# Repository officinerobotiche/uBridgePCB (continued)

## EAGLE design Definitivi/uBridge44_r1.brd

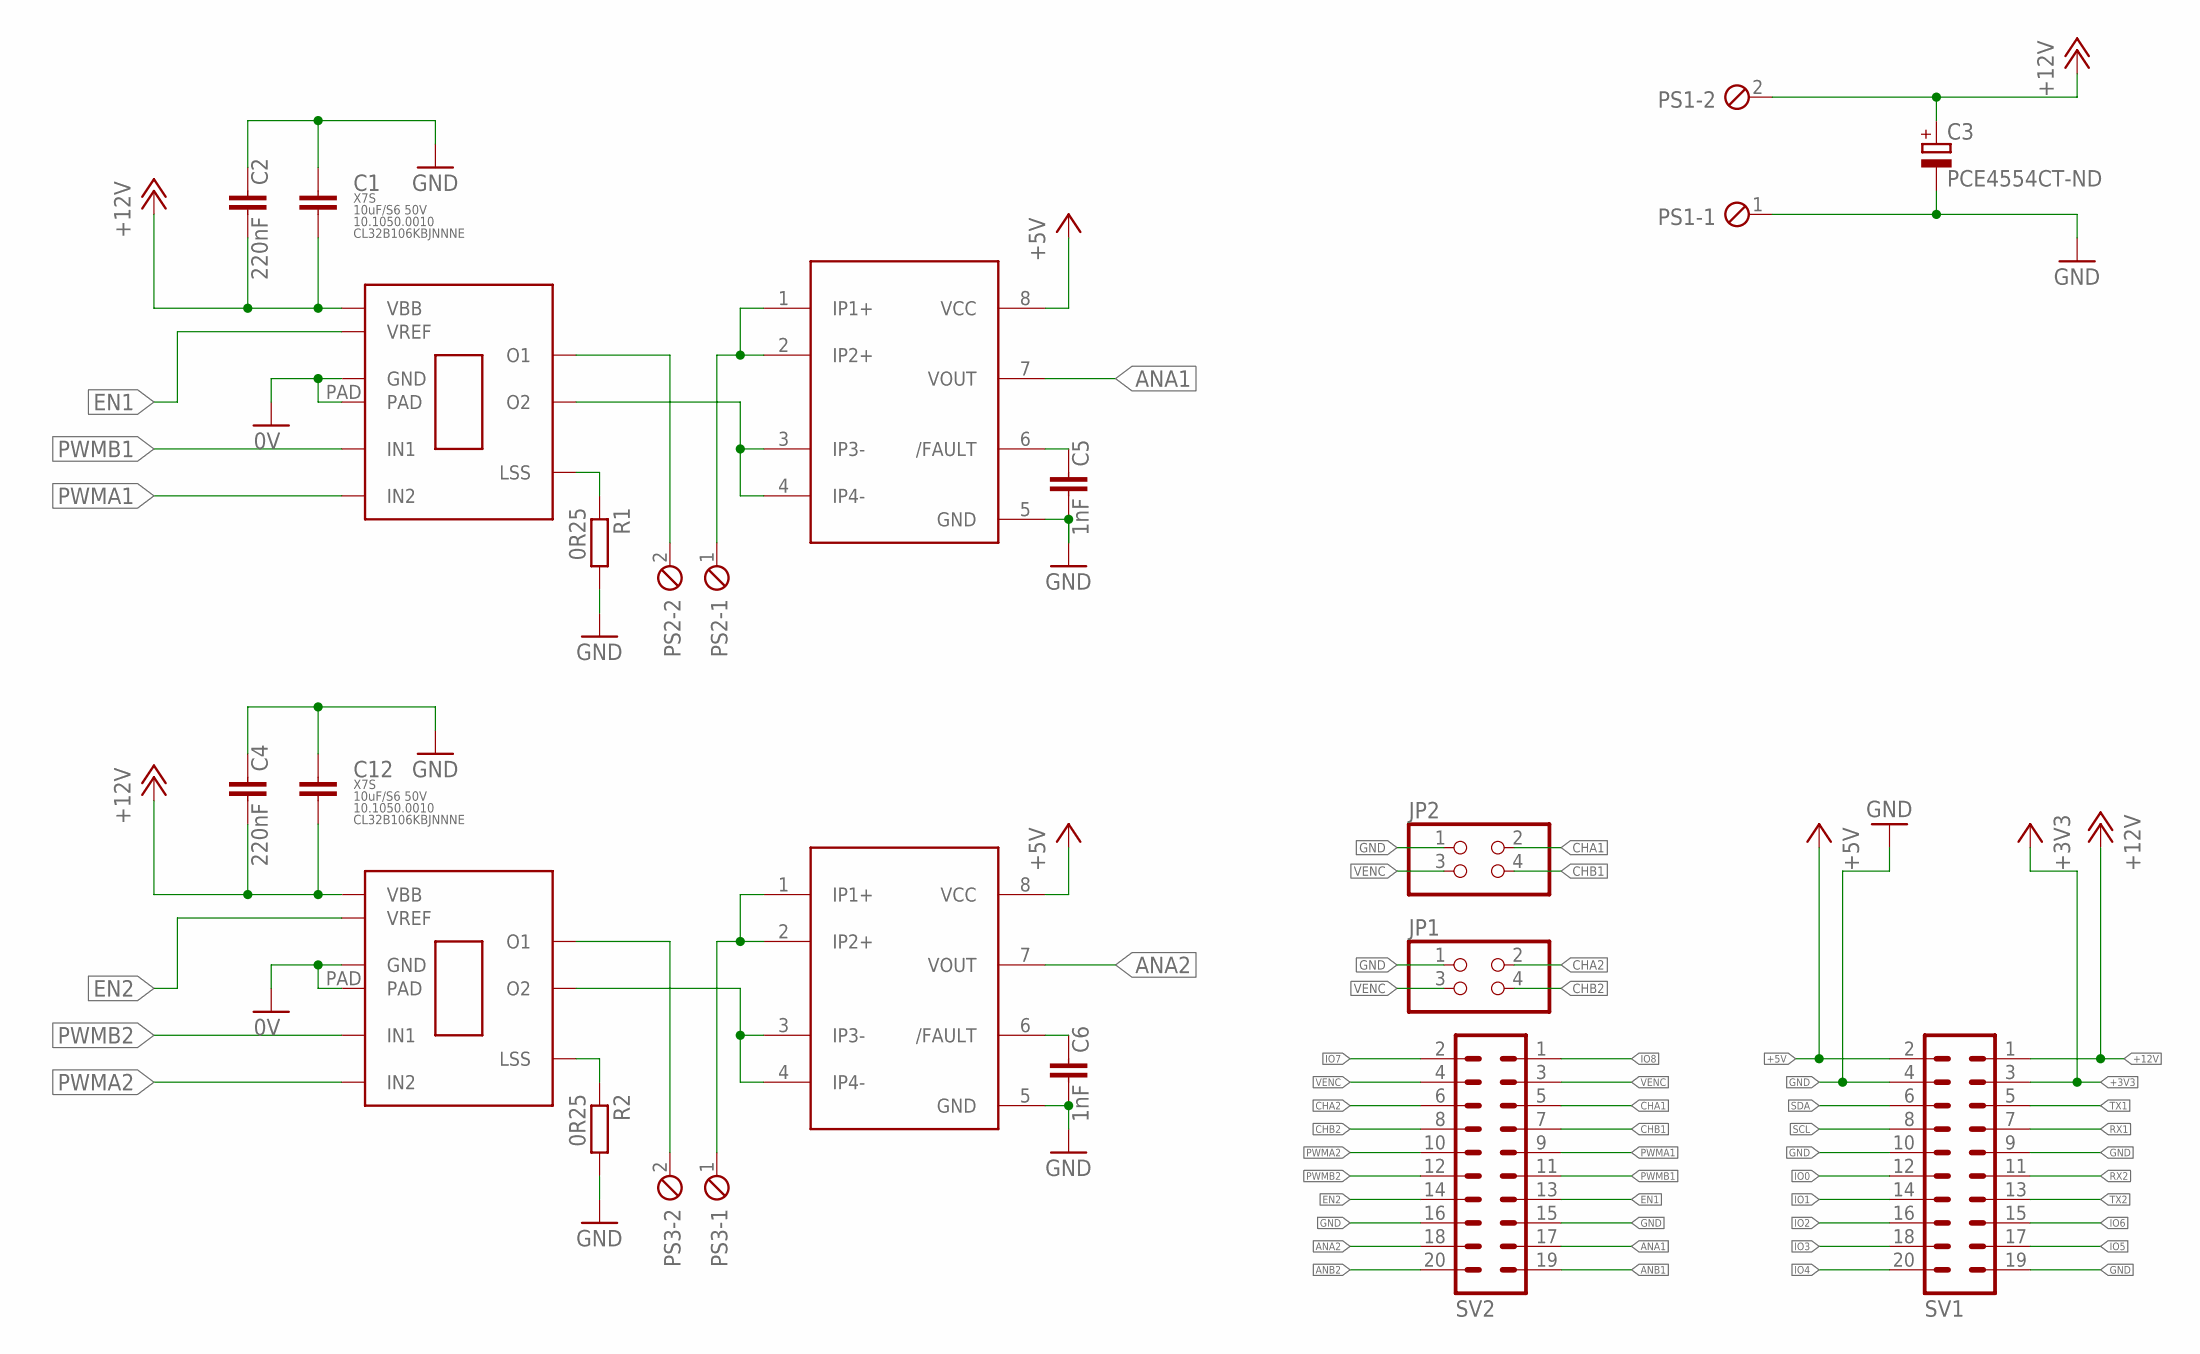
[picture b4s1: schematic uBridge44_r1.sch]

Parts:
C1, C12: 10uF/S6 50V; C3225
C2, C4: 220nF; C0805K
C3: PCE4554CT-ND; UD-6,3X7,7_NICHICON
C5, C6: 1nF; C0805K
JP1, JP2: PINHD-2X2; 2X02
PS1, PS2, PS3: MPT2; 2POL254
R1, R2: 0R25; R1206
SV1, SV2: MA10-2
U$1, U$2: A4950; SOICN
U$3, U$4: ACS723; SO08

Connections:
+3V3: SV1.3
+5V: SV1.2, U$3.8 (VCC), U$4.8 (VCC)
+12V: C1.2, C2.2, C3.+, C4.2, C12.2, PS1.2, SV1.1, U$1.5VCC (VBB), U$2.5VCC (VBB)
ANA1: SV2.17, U$3.7 (VOUT)
ANA2: SV2.18, U$4.7 (VOUT)
ANB1: SV2.19
ANB2: SV2.20
CHA1: JP2.2, SV2.5
CHA2: JP1.2, SV2.6
CHB1: JP2.4, SV2.7
CHB2: JP1.4, SV2.8
EN1: SV2.13, U$1.4CS (VREF)
EN2: SV2.14, U$2.4CS (VREF)
GND: C1.1, C2.1, C3.-, C4.1, C5.2, C6.2, C12.1, JP1.1, JP2.1, PS1.1, R1.2, R2.2, SV1.4, SV1.9, SV1.10, SV1.19, SV2.15, SV2.16, U$1.1VIN (GND), U$1.PAD, U$2.1VIN (GND), U$2.PAD, U$3.5 (GND), U$4.5 (GND)
IO0: SV1.12
IO1: SV1.14
IO2: SV1.16
IO3: SV1.18
IO4: SV1.20
IO5: SV1.17
IO6: SV1.15
IO7: SV2.2
IO8: SV2.1
unnamed: R2.1, U$2.7BOOT (LSS)
unnamed: PS3.2, U$2.6GND (O1)
unnamed: U$2.8SW (O2), U$4.3 (IP3-), U$4.4 (IP4-)
unnamed: C5.1, U$3.6 (/FAULT)
unnamed: C6.1, U$4.6 (/FAULT)
unnamed: PS2.1, U$3.1 (IP1+), U$3.2 (IP2+)
unnamed: PS2.2, U$1.6GND (O1)
unnamed: PS3.1, U$4.1 (IP1+), U$4.2 (IP2+)
unnamed: R1.1, U$1.7BOOT (LSS)
unnamed: U$1.8SW (O2), U$3.3 (IP3-), U$3.4 (IP4-)
PWMA1: SV2.9, U$1.2TON (IN2)
PWMA2: SV2.10, U$2.2TON (IN2)
PWMB1: SV2.11, U$1.3EN (IN1)
PWMB2: SV2.12, U$2.3EN (IN1)
RX1: SV1.7
RX2: SV1.11
SCL: SV1.8
SDA: SV1.6
TX1: SV1.5
TX2: SV1.13
VENC: JP1.3, JP2.3, SV2.3, SV2.4

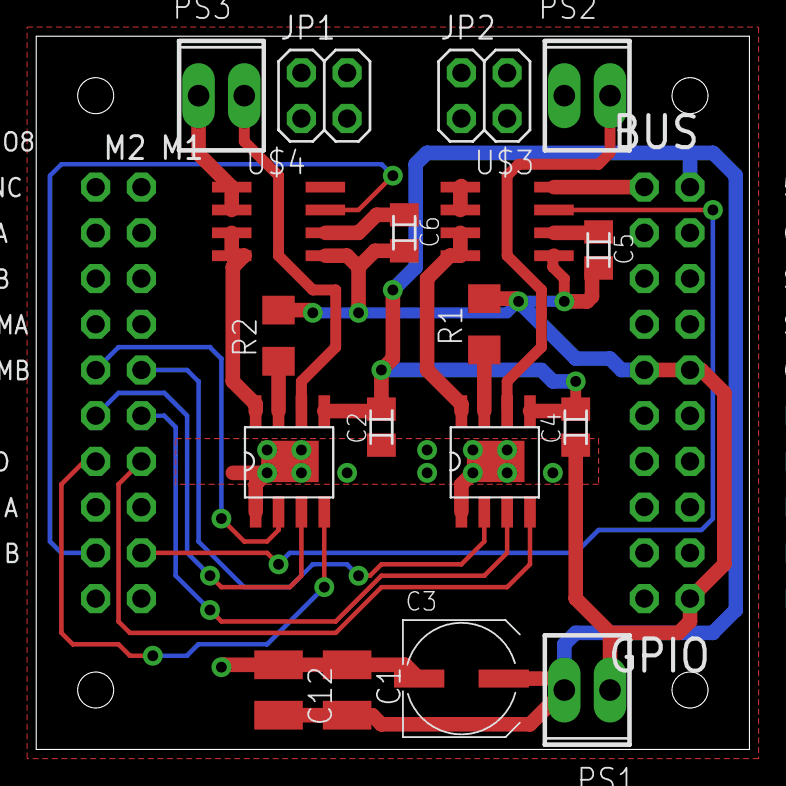
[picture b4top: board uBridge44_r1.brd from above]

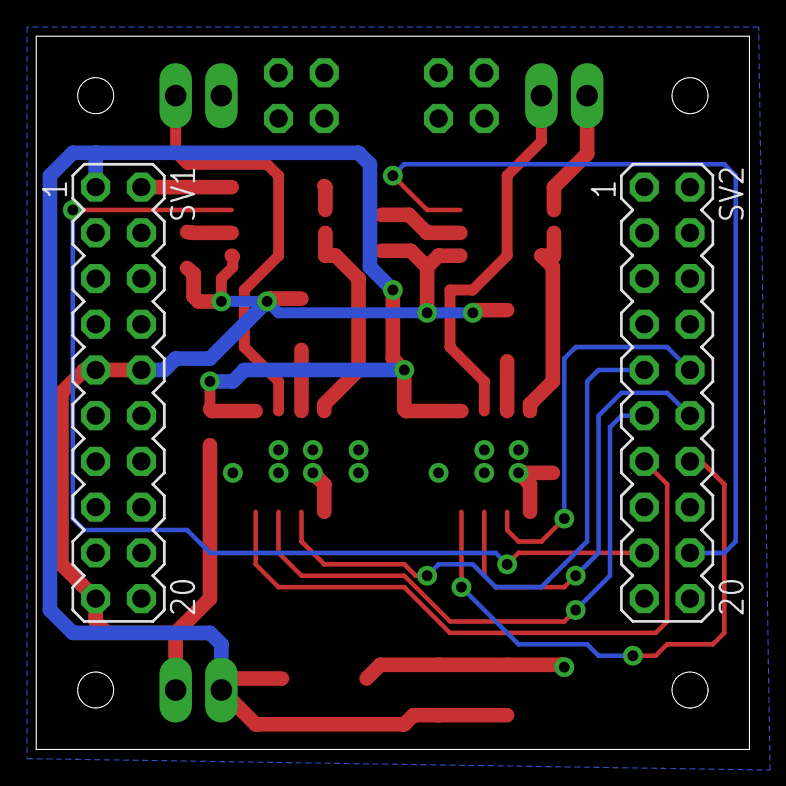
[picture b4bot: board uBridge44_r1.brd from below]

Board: 2 copper layers, 39.6 x 39.6 mm, 20 parts (2 on the bottom side), 26 nets.

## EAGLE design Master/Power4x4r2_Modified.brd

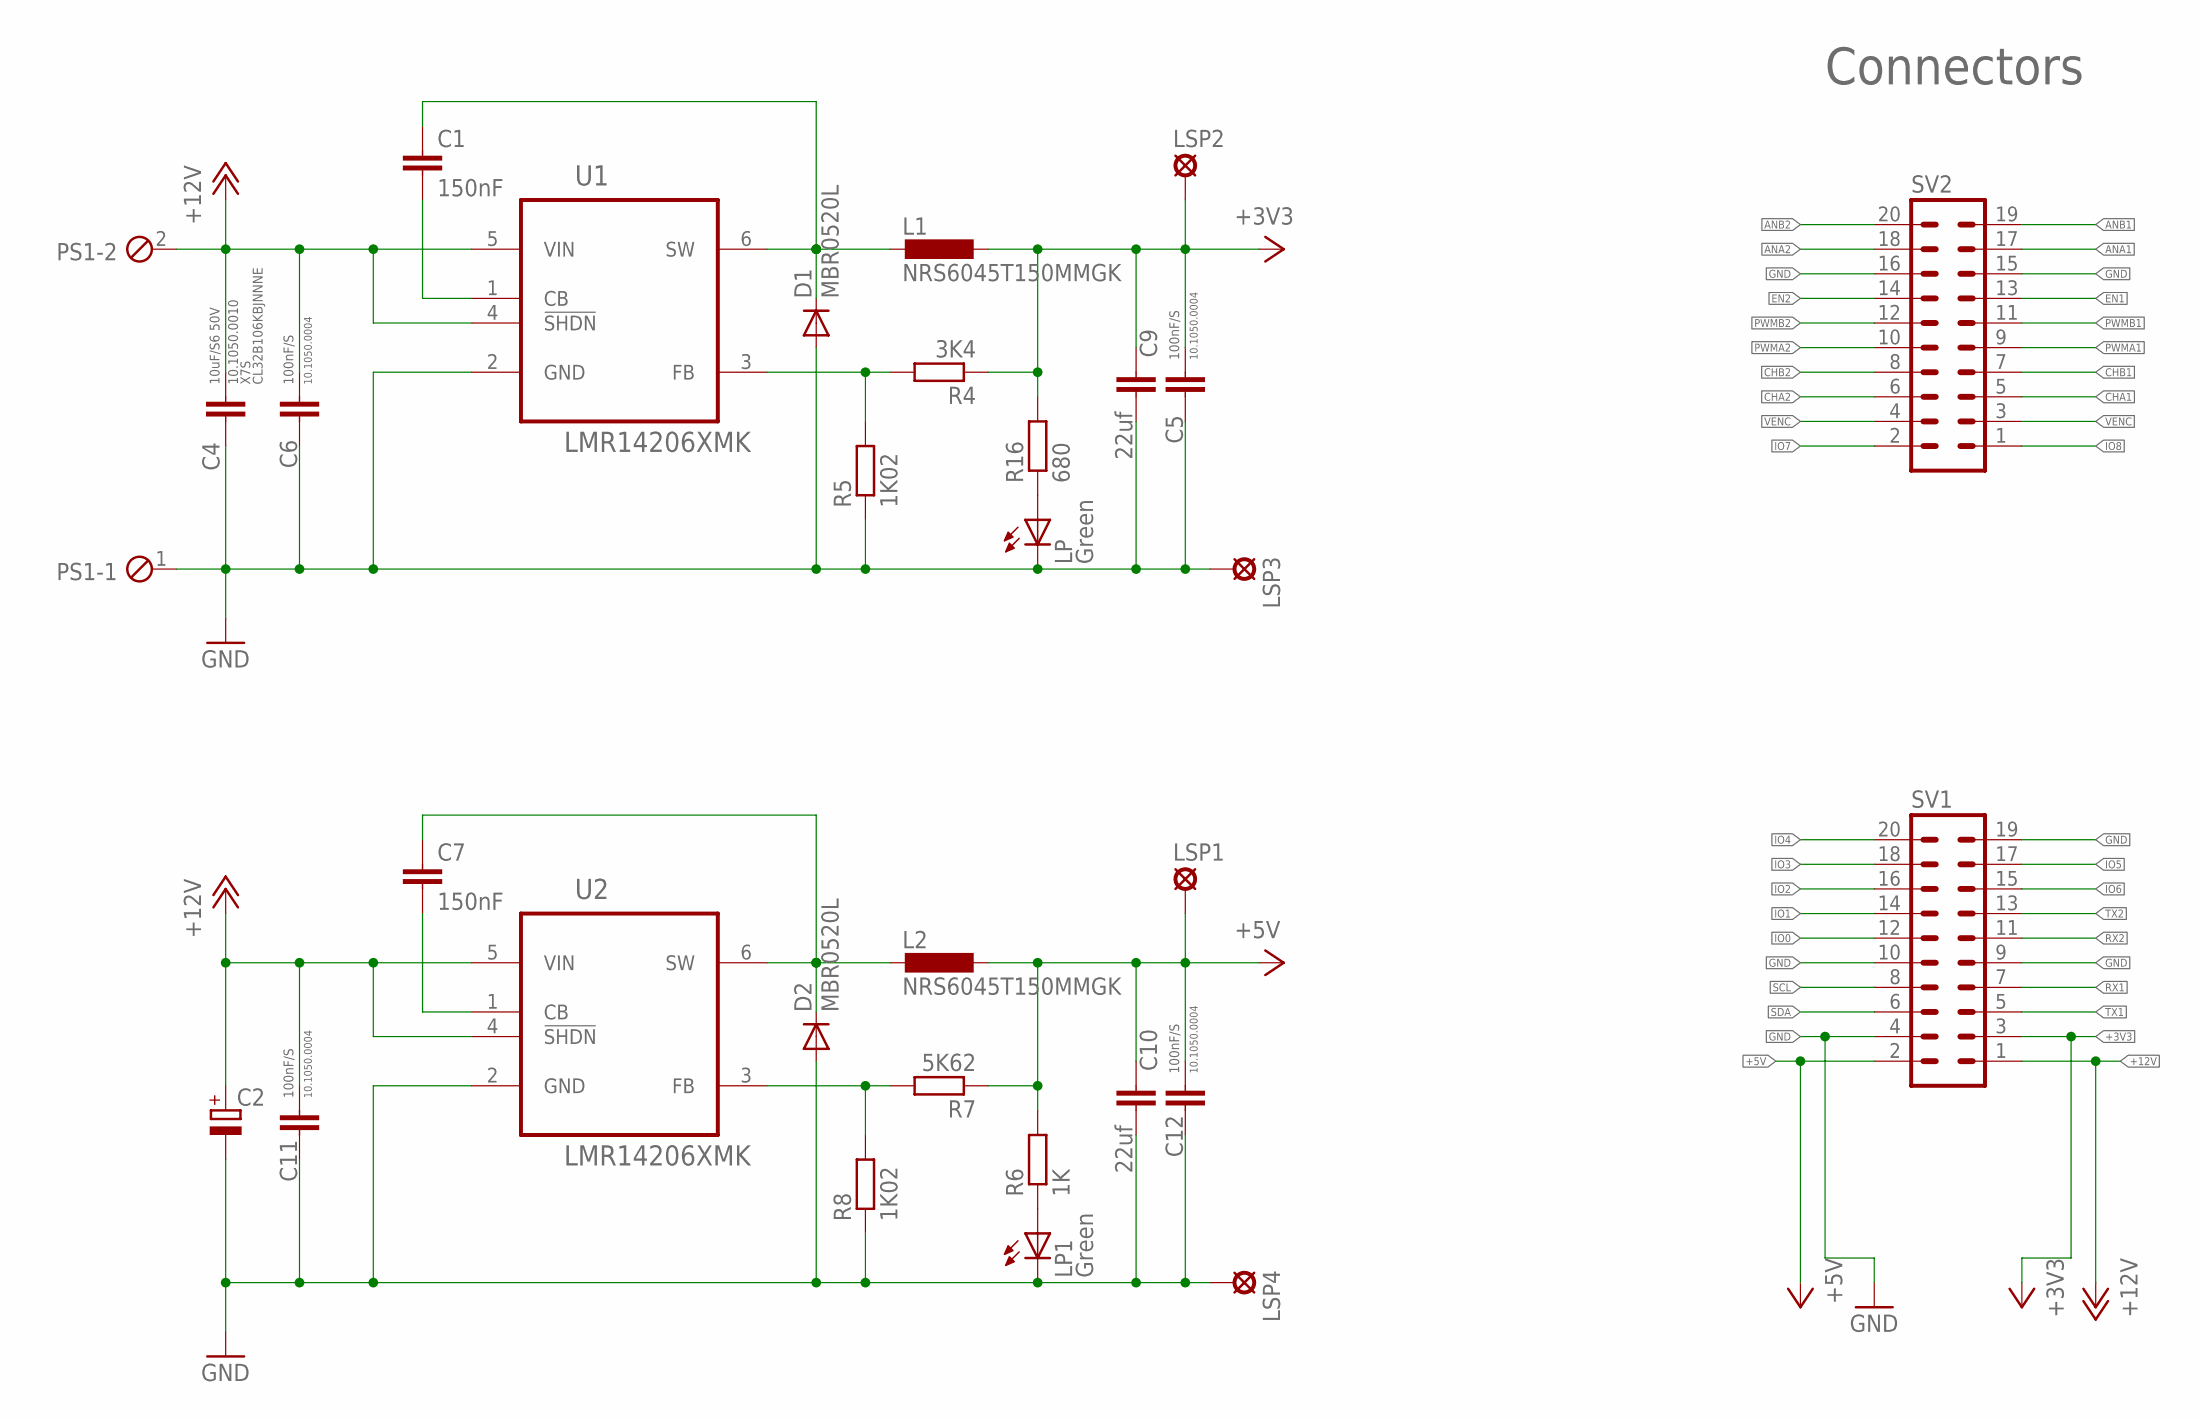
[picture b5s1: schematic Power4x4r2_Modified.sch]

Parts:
C1, C7: 150nF; C0805K
C2: CPOL-EUUD-6,3X7,7; UD-6,3X7,7_NICHICON
C4: 10uF/S6 50V; C3225
C5, C6, C11, C12: 100nF/S; C0805
C9, C10: 22uf; C1206
D1, D2: MBR0520L; SOD123; DIGIKEY MBR0520LCT-ND
L1, L2: NRS6045T150MMGK; POWER-CHOKE_WE-TPC; DIGIKEY 587-2948-1-ND
LP, LP1: Green; CHIPLED_0805
LSP1, LSP2, LSP3, LSP4: LSP10
PS1: MPT2; 2POL254
R4: 3K4; R0805
R5, R8: 1K02; R0805
R6: 1K; R0603
R7: 5K62; R0805
R16: 680; R0603
SV1, SV2: MA10-2
U1, U2: LMR14206XMK; SOT95P280X110-6N; DIGIKEY LMR14206XMKE/NOPBCT-ND

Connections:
+3V3: C5.2, C9.1, L1.1, LSP2.MP, R4.1, R16.2, SV1.3
+5V: C10.1, C12.2, L2.1, LSP1.MP, R6.2, R7.1, SV1.2
+12V: C2.+, C4.1, C6.2, C11.2, PS1.2, SV1.1, U1.4 (!SHDN), U1.5 (VIN), U2.4 (!SHDN), U2.5 (VIN)
ANA1: SV2.17
ANA2: SV2.18
ANB1: SV2.19
ANB2: SV2.20
CHA1: SV2.5
CHA2: SV2.6
CHB1: SV2.7
CHB2: SV2.8
EN1: SV2.13
EN2: SV2.14
GND: C2.-, C4.2, C5.1, C6.1, C9.2, C10.2, C11.1, C12.1, D1.A, D2.A, LP.C, LP1.C, LSP3.MP, LSP4.MP, PS1.1, R5.1, R8.1, SV1.4, SV1.9, SV1.10, SV1.19, SV2.15, SV2.16, U1.2 (GND), U2.2 (GND)
IO0: SV1.12
IO1: SV1.14
IO2: SV1.16
IO3: SV1.18
IO4: SV1.20
IO5: SV1.17
IO6: SV1.15
IO7: SV2.2
IO8: SV2.1
unnamed: C1.2, U1.1 (CB)
unnamed: C1.1, D1.C, L1.2, U1.6 (SW)
unnamed: LP1.A, R6.1
unnamed: R4.2, R5.2, U1.3 (FB)
unnamed: LP.A, R16.1
unnamed: C7.2, U2.1 (CB)
unnamed: C7.1, D2.C, L2.2, U2.6 (SW)
unnamed: R7.2, R8.2, U2.3 (FB)
PWMA1: SV2.9
PWMA2: SV2.10
PWMB1: SV2.11
PWMB2: SV2.12
RX1: SV1.7
RX2: SV1.11
SCL: SV1.8
SDA: SV1.6
TX1: SV1.5
TX2: SV1.13
VENC: SV2.3, SV2.4

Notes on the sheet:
Connectors

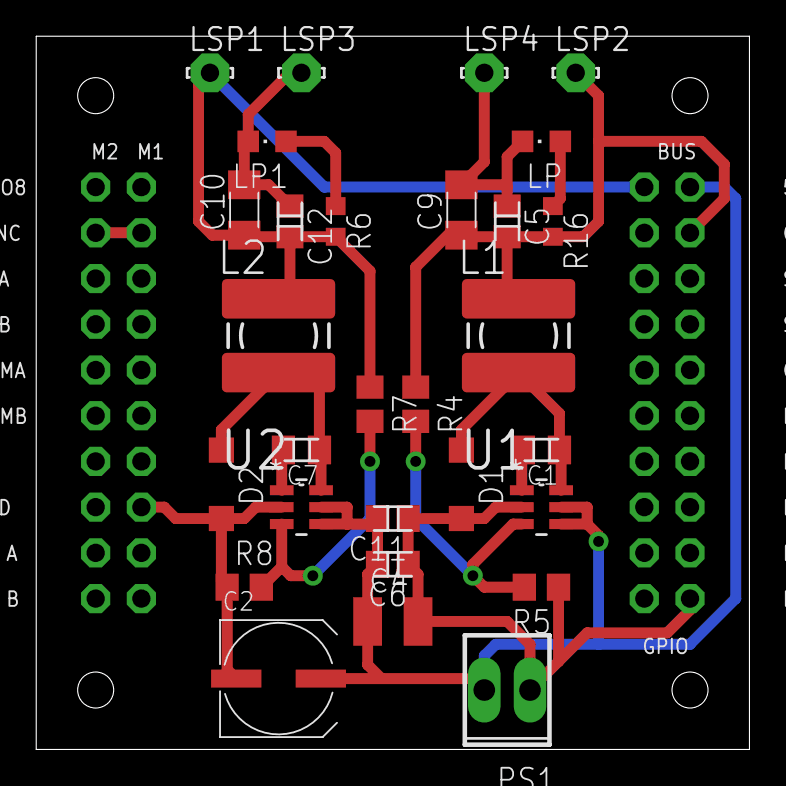
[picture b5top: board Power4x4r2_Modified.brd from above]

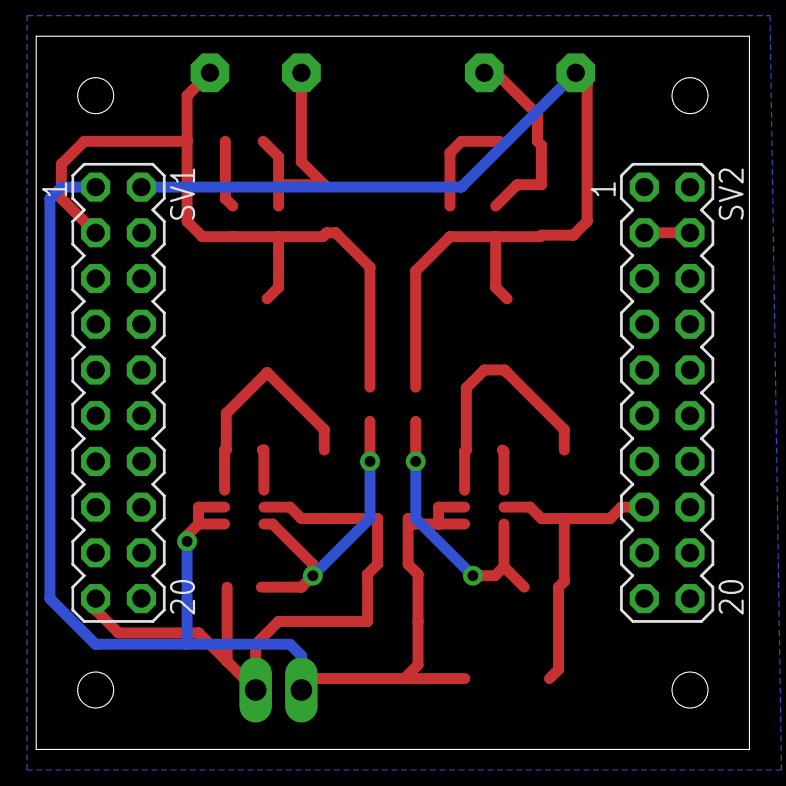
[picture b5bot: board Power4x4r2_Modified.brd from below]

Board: 2 copper layers, 39.6 x 39.6 mm, 31 parts (2 on the bottom side), 13 nets.

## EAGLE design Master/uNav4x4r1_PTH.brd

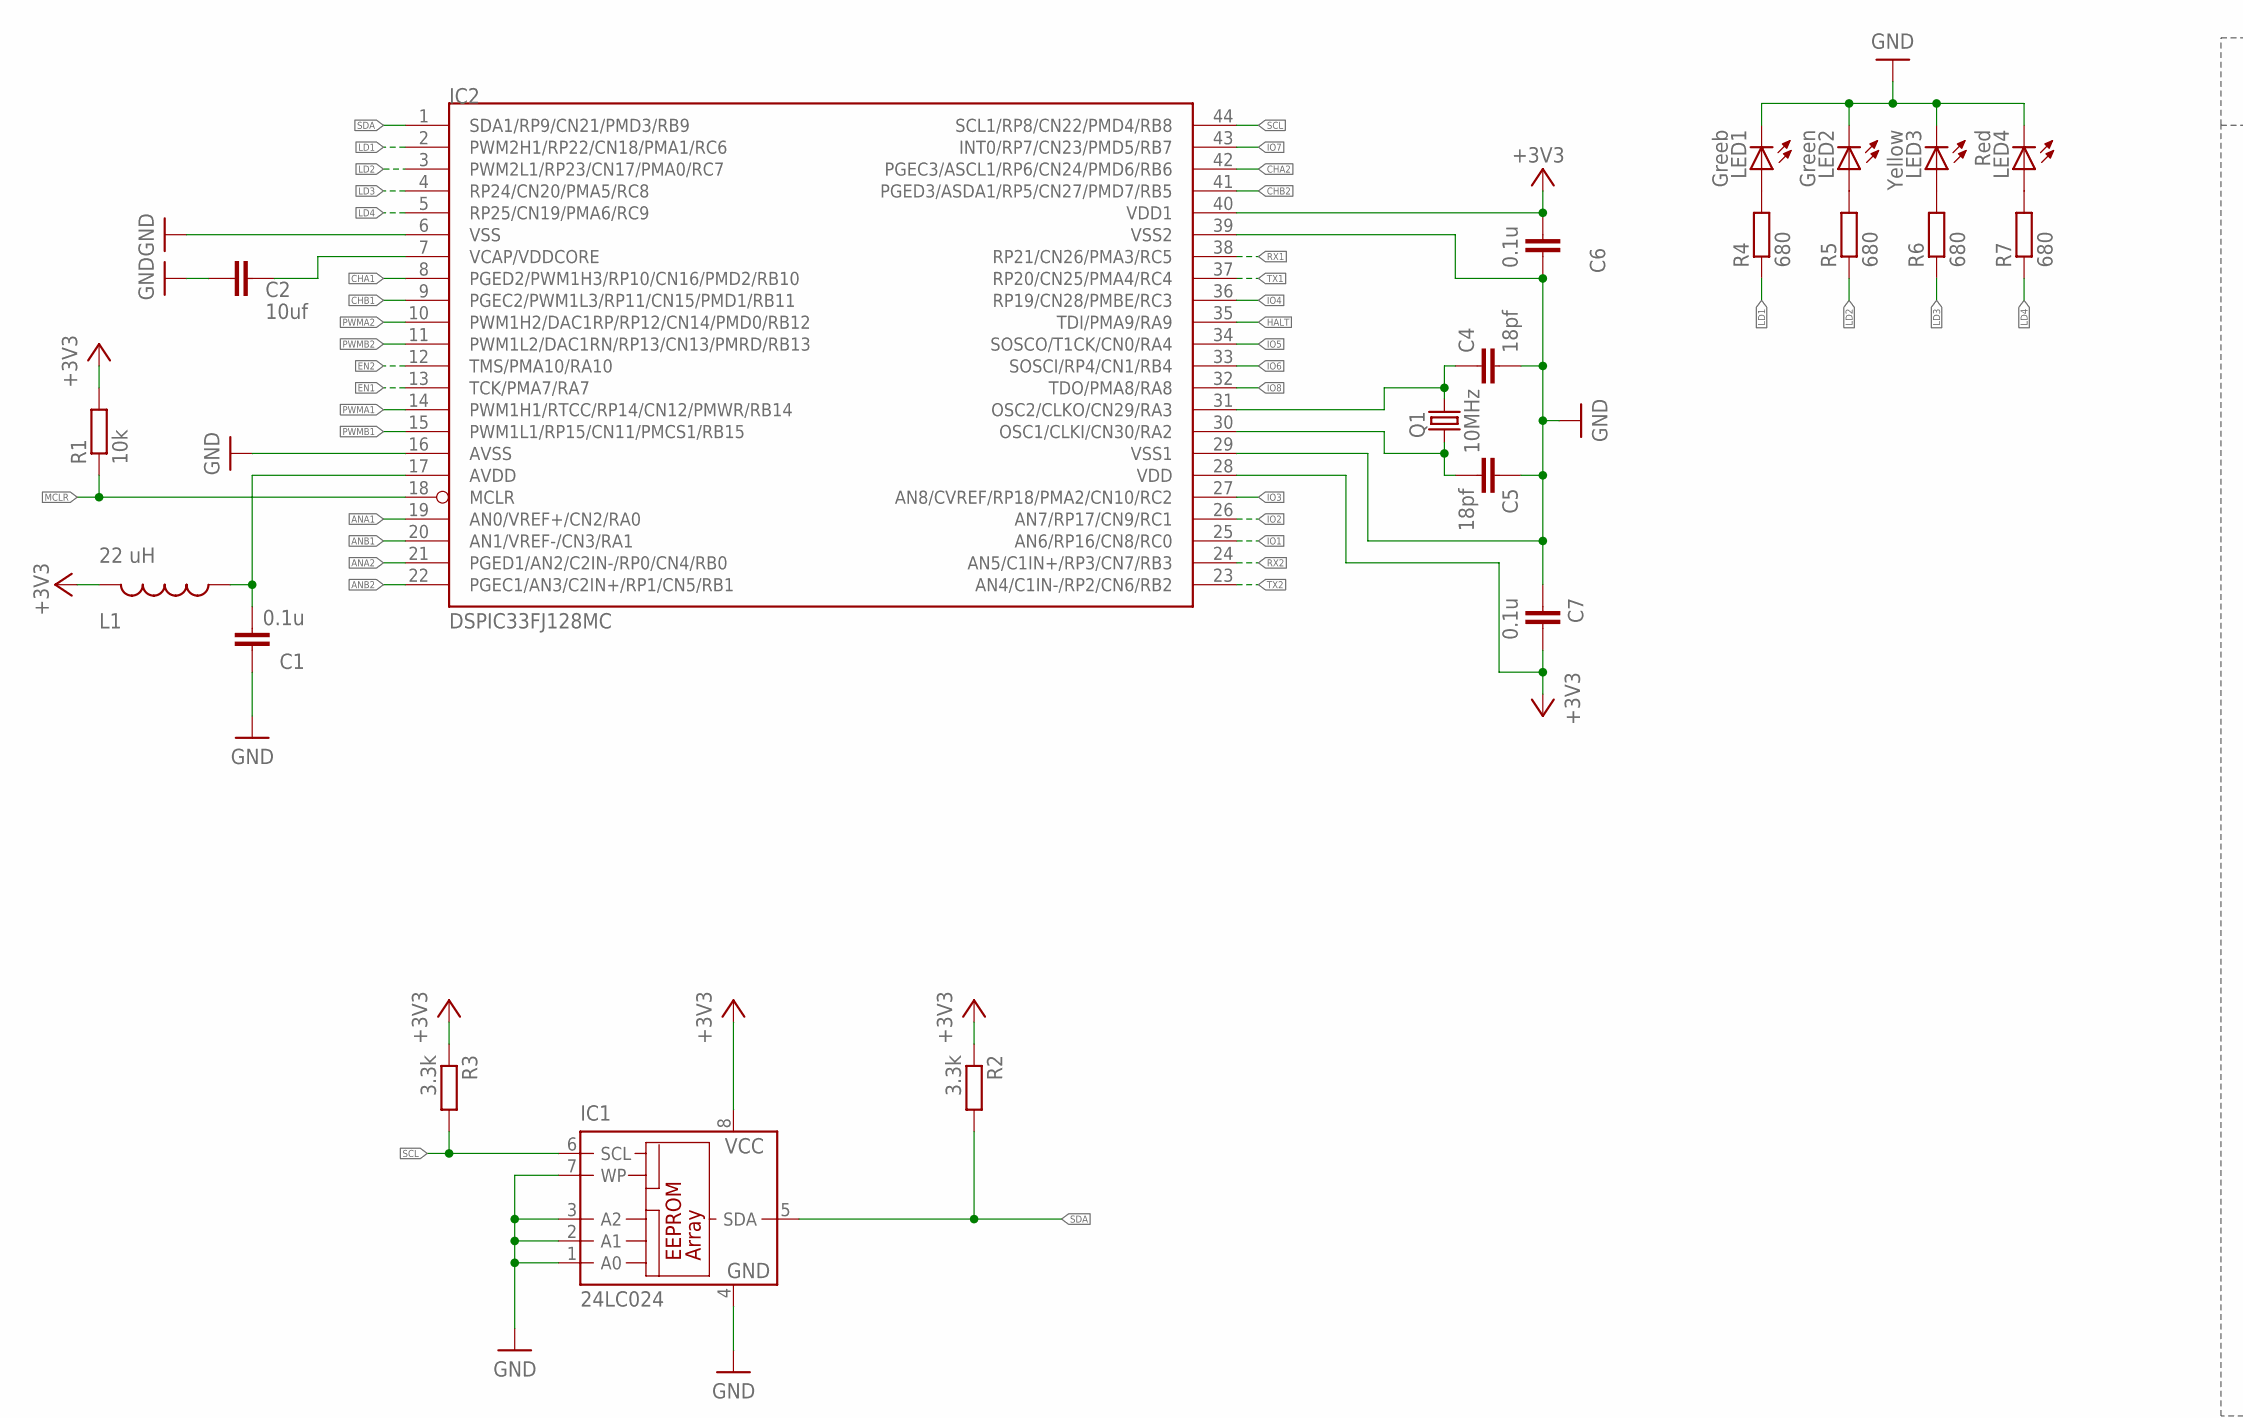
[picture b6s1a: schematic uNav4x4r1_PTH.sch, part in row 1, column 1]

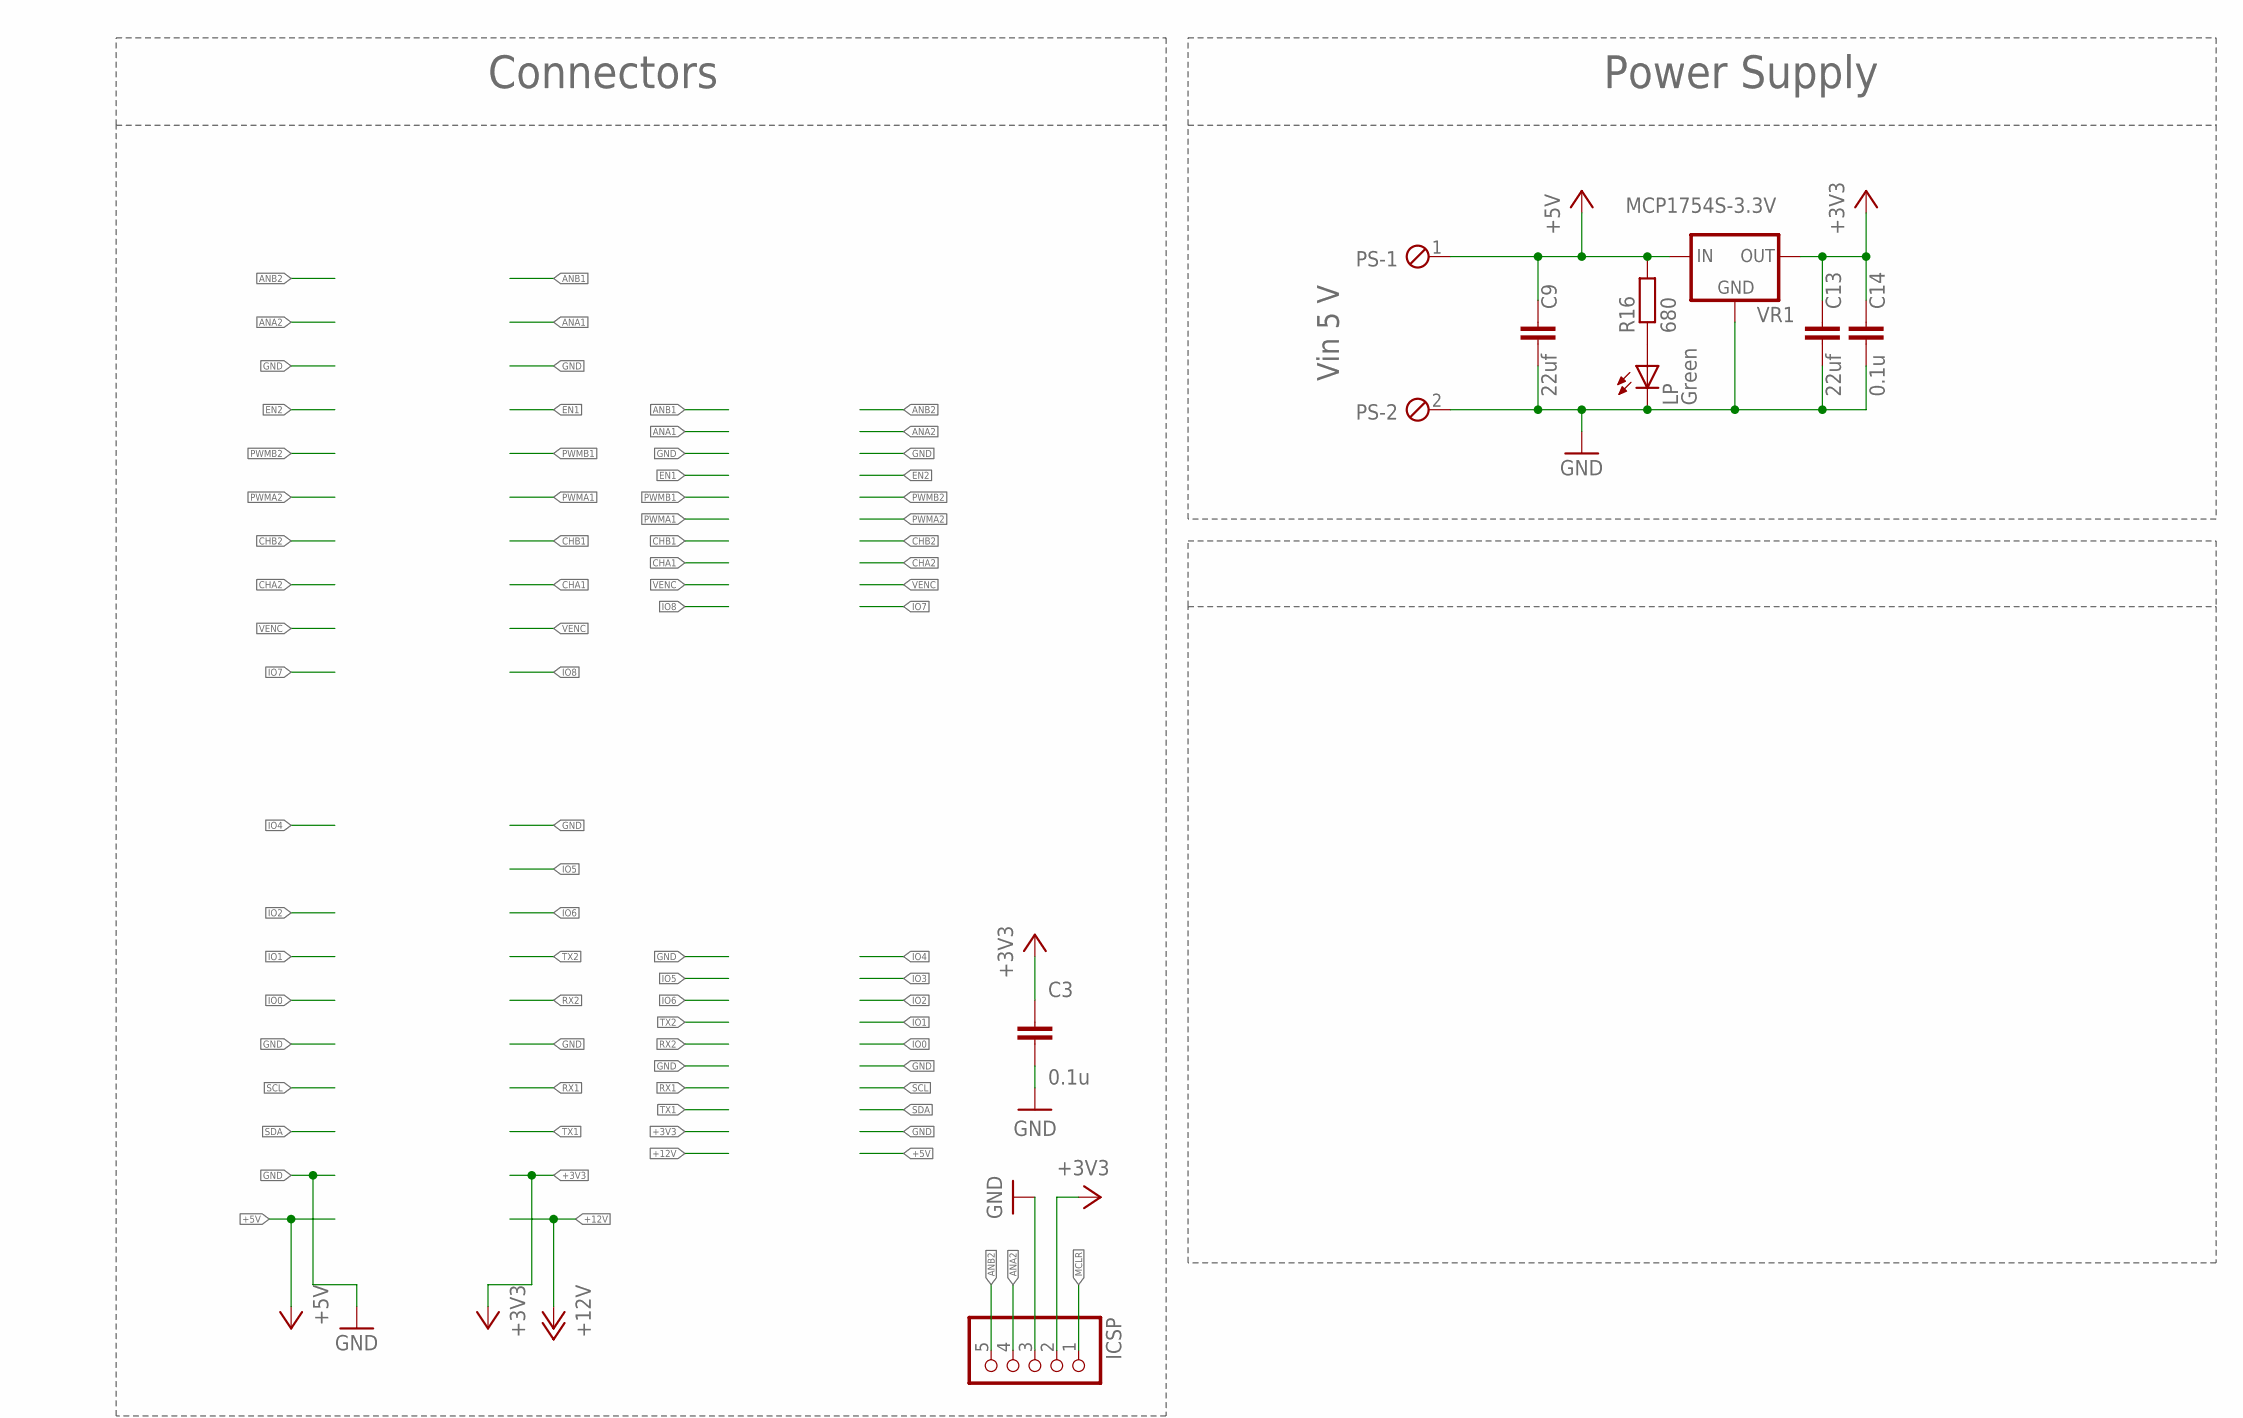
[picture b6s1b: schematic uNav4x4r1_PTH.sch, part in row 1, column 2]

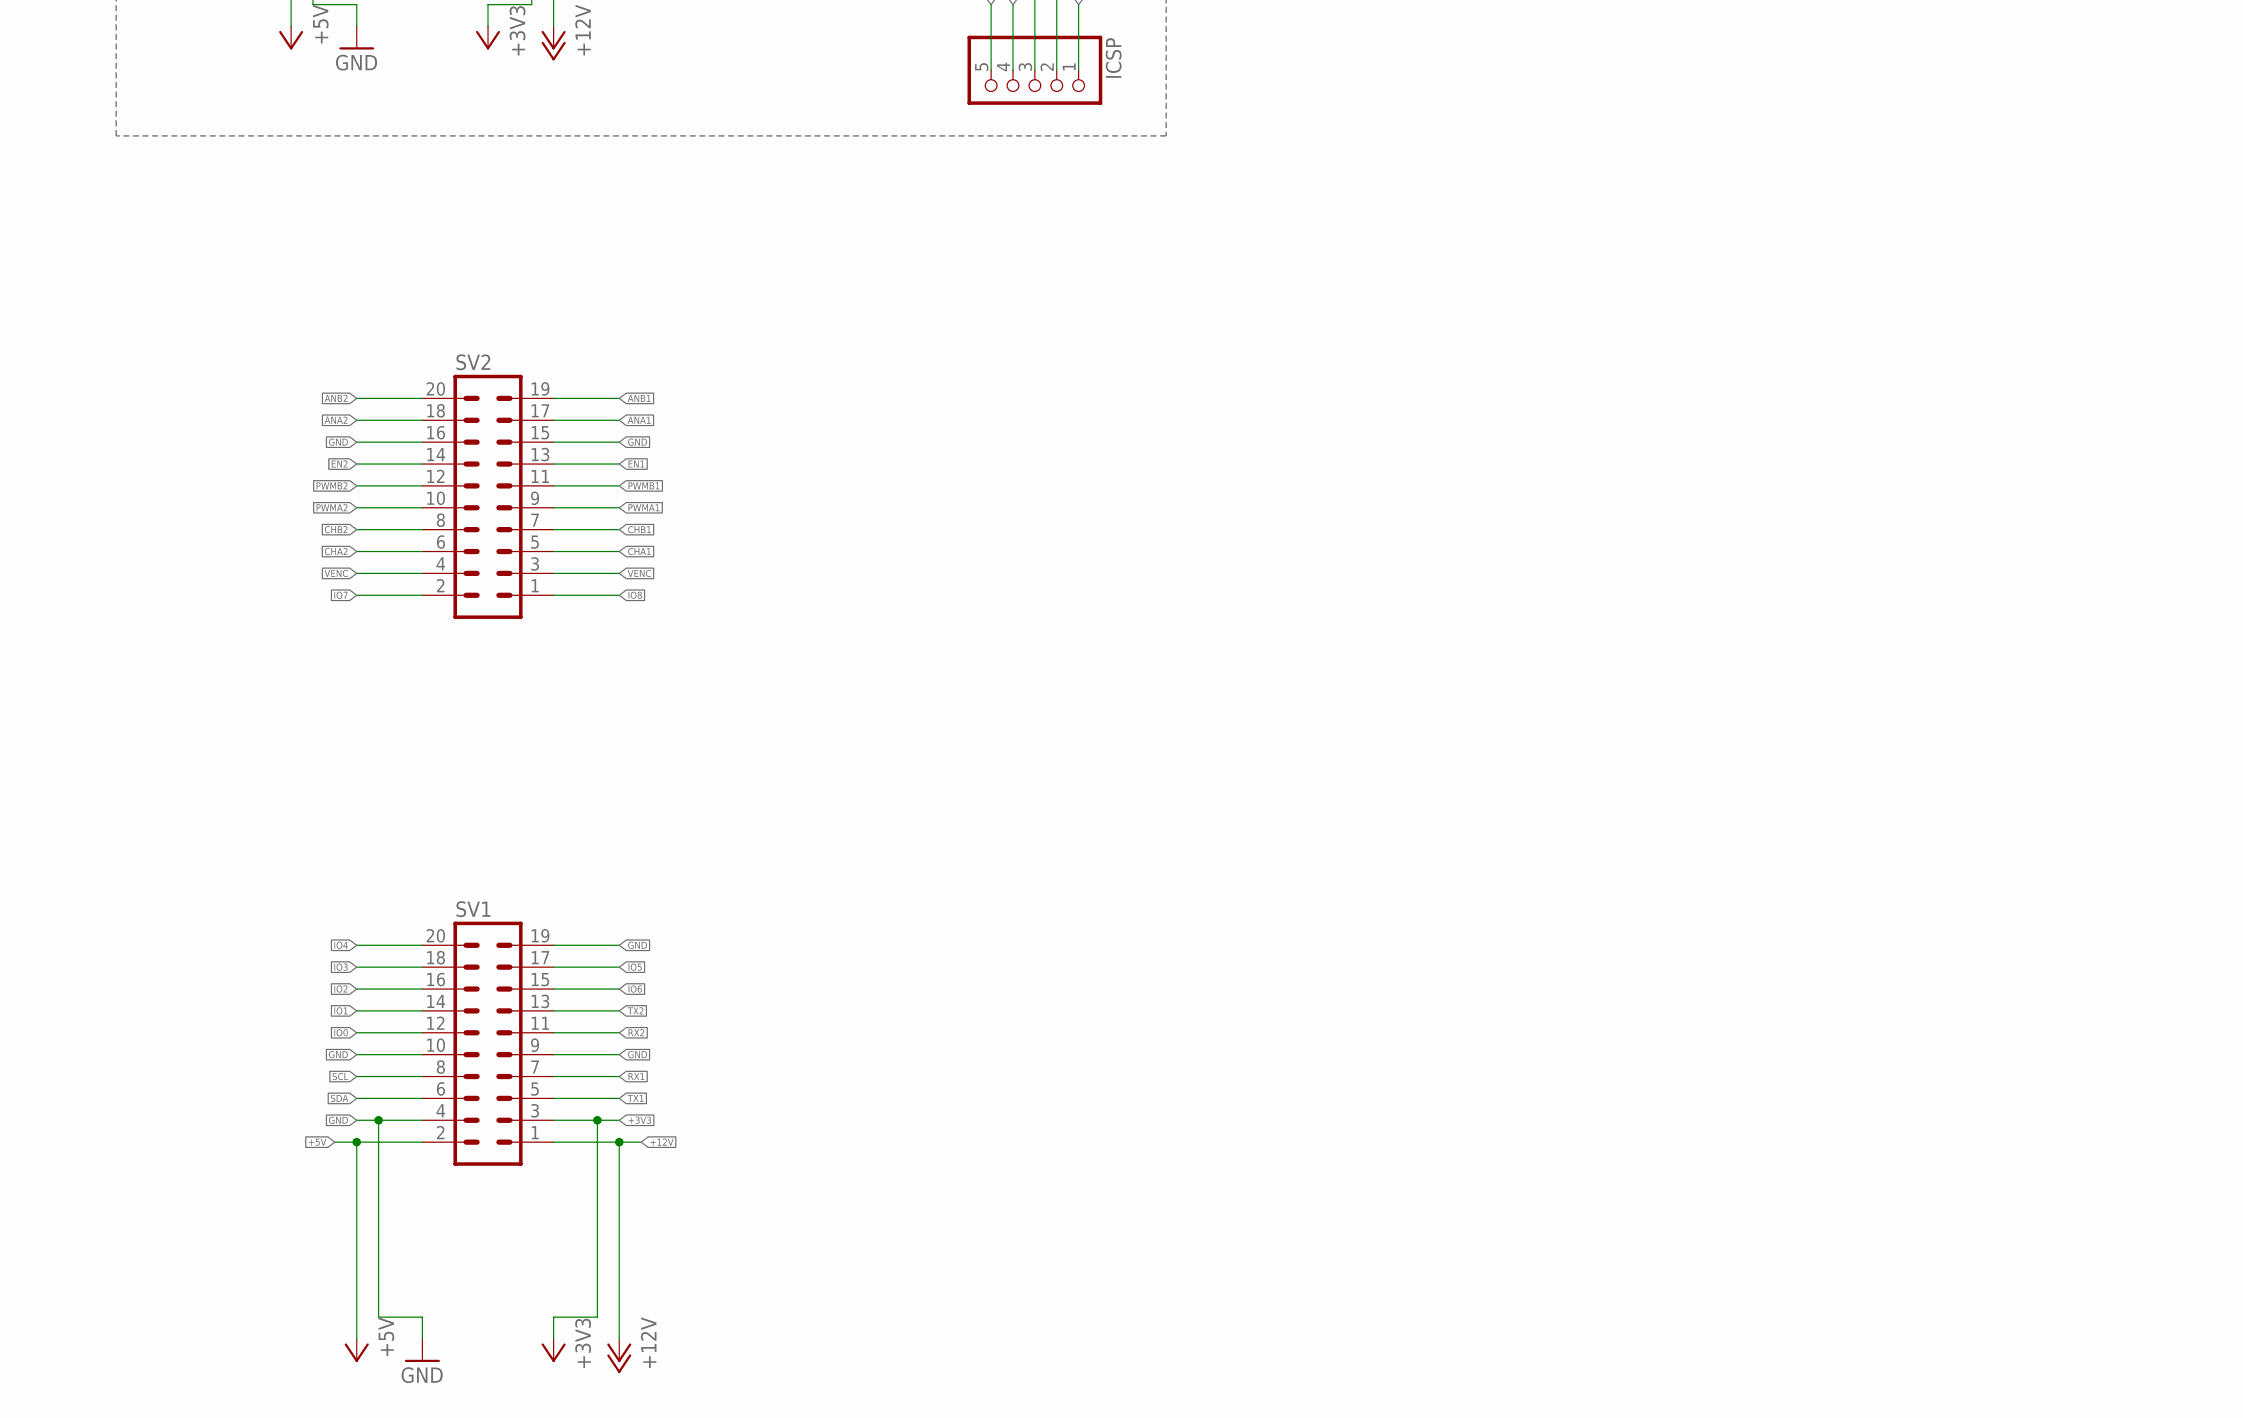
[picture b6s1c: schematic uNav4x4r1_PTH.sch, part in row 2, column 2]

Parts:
C1, C3, C6, C7, C14: 0.1u; C0603
C2: 10uf; C1206
C4, C5: 18pf; C0603
C9, C13: 22uf; C1206
IC1: 24LC024; SO-08M
IC2: DSPIC33FJ128MC; TQFP44
ICSP: PINHD-1X05_2.54-S; 1X05-S
L1: 22 uH; 0805
LED1: Greeb; CHIPLED_0805
LED2: Green; CHIPLED_0805
LED3: Yellow; CHIPLED_0805
LED4: Red; CHIPLED_0805
LP: Green; CHIPLED_0805
PS: MPT2; 2POL254
Q1: 10MHz; HC49U-V
R1: 10k; R0603
R2, R3: 3.3k; R0603
R4, R5, R6, R7, R16: 680; R0603
SV1, SV2: MA10-2
VR1: MCP1754S-3.3V; SOT89

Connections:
+3V3: C3.1, C6.2, C7.1, C13.1, C14.1, IC1.8 (VCC), IC2.28 (VDD), IC2.40 (VDD1), ICSP.2, L1.2, R1.2, R2.1, R3.1, SV1.3, VR1.3 (OUT)
+5V: C9.1, PS.1, R16.2, SV1.2, VR1.1 (IN)
+12V: SV1.1
ANA1: IC2.19 (AN0/VREF+/CN2/RA0), SV2.17
ANA2: IC2.21 (PGED1/AN2/C2IN-/RP0/CN4/RB0), ICSP.4, SV2.18
ANB1: IC2.20 (AN1/VREF-/CN3/RA1), SV2.19
ANB2: IC2.22 (PGEC1/AN3/C2IN+/RP1/CN5/RB1), ICSP.5, SV2.20
AVDD: C1.2, IC2.17 (AVDD), L1.1
CHA1: IC2.8 (PGED2/PWM1H3/RP10/CN16/PMD2/RB10), SV2.5
CHA2: IC2.42 (PGEC3/ASCL1/RP6/CN24/PMD6/RB6), SV2.6
CHB1: IC2.9 (PGEC2/PWM1L3/RP11/CN15/PMD1/RB11), SV2.7
CHB2: IC2.41 (PGED3/ASDA1/RP5/CN27/PMD7/RB5), SV2.8
EN1: IC2.13 (TCK/PMA7/RA7), SV2.13
EN2: IC2.12 (TMS/PMA10/RA10), SV2.14
GND: C1.1, C2.2, C3.2, C4.2, C5.1, C6.1, C7.2, C9.2, C13.2, C14.2, IC1.1 (A0), IC1.2 (A1), IC1.3 (A2), IC1.4 (GND), IC1.7 (WP), IC2.6 (VSS), IC2.16 (AVSS), IC2.29 (VSS1), IC2.39 (VSS2), ICSP.3, LED1.C, LED2.C, LED3.C, LED4.C, LP.C, PS.2, SV1.4, SV1.9, SV1.10, SV1.19, SV2.15, SV2.16, VR1.2 (GND), VR1.4 (GND)
HALT: IC2.35 (TDI/PMA9/RA9)
IO0: SV1.12
IO1: IC2.25 (AN6/RP16/CN8/RC0), SV1.14
IO2: IC2.26 (AN7/RP17/CN9/RC1), SV1.16
IO3: IC2.27 (AN8/CVREF/RP18/PMA2/CN10/RC2), SV1.18
IO4: IC2.36 (RP19/CN28/PMBE/RC3), SV1.20
IO5: IC2.34 (SOSCO/T1CK/CN0/RA4), SV1.17
IO6: IC2.33 (SOSCI/RP4/CN1/RB4), SV1.15
IO7: IC2.43 (INT0/RP7/CN23/PMD5/RB7), SV2.2
IO8: IC2.32 (TDO/PMA8/RA8), SV2.1
LD1: IC2.2 (PWM2H1/RP22/CN18/PMA1/RC6), R4.1
LD2: IC2.3 (PWM2L1/RP23/CN17/PMA0/RC7), R5.1
LD3: IC2.4 (RP24/CN20/PMA5/RC8), R6.1
LD4: IC2.5 (RP25/CN19/PMA6/RC9), R7.1
MCLR: IC2.18 (MCLR), ICSP.1, R1.1
unnamed: C5.2, IC2.30 (OSC1/CLKI/CN30/RA2), Q1.1
unnamed: C4.1, IC2.31 (OSC2/CLKO/CN29/RA3), Q1.2
unnamed: LP.A, R16.1
unnamed: LED1.A, R4.2
unnamed: LED2.A, R5.2
unnamed: LED3.A, R6.2
unnamed: LED4.A, R7.2
PWMA1: IC2.14 (PWM1H1/RTCC/RP14/CN12/PMWR/RB14), SV2.9
PWMA2: IC2.10 (PWM1H2/DAC1RP/RP12/CN14/PMD0/RB12), SV2.10
PWMB1: IC2.15 (PWM1L1/RP15/CN11/PMCS1/RB15), SV2.11
PWMB2: IC2.11 (PWM1L2/DAC1RN/RP13/CN13/PMRD/RB13), SV2.12
RX1: IC2.38 (RP21/CN26/PMA3/RC5), SV1.7
RX2: IC2.24 (AN5/C1IN+/RP3/CN7/RB3), SV1.11
SCL: IC1.6 (SCL), IC2.44 (SCL1/RP8/CN22/PMD4/RB8), R3.2, SV1.8
SDA: IC1.5 (SDA), IC2.1 (SDA1/RP9/CN21/PMD3/RB9), R2.2, SV1.6
TX1: IC2.37 (RP20/CN25/PMA4/RC4), SV1.5
TX2: IC2.23 (AN4/C1IN-/RP2/CN6/RB2), SV1.13
VCAP/VDDCORE: C2.1, IC2.7 (VCAP/VDDCORE)
VENC: SV2.3, SV2.4

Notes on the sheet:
Connectors
Vin 5 V
Power Supply
